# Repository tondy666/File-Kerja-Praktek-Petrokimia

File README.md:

File Laporan Kerja Praktek PT.PETROKIMIA GRESIK

© Copyright
Tondy_666

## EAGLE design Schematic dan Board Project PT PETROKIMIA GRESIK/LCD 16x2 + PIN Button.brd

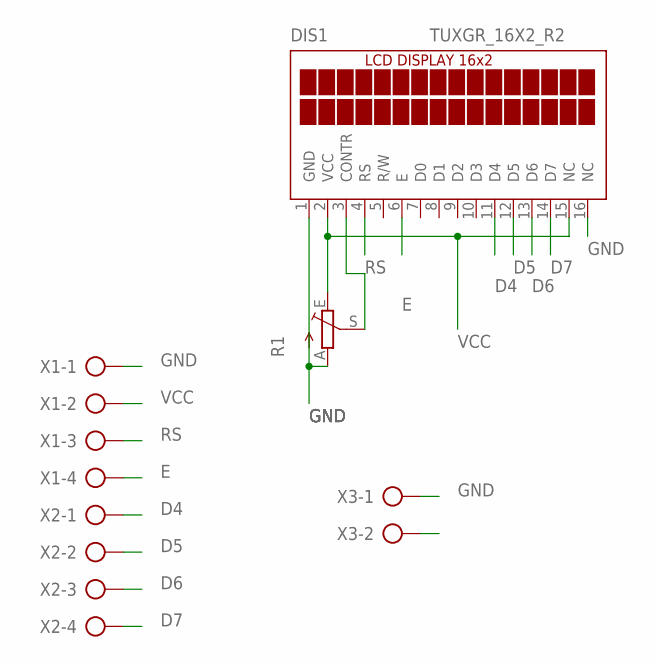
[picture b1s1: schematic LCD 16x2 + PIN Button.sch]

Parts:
DIS1: TUXGR_16X2_R2
R1: TRIM_EU-B25P; B25P
X1, X2: AK500/4-H
X3: AK500/2-H

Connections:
D4: DIS1.11 (D4), X2.1
D5: DIS1.12 (D5), X2.2
D6: DIS1.13 (D6), X2.3
D7: DIS1.14 (D7), X2.4
E: DIS1.6 (E), X1.4
GND: DIS1.1 (GND), DIS1.16 (NC), R1.A, X1.1, X3.1
unnamed: DIS1.3 (CONTR), R1.S
RS: DIS1.4 (RS), X1.3
VCC: DIS1.2 (VCC), DIS1.15 (NC), R1.E, X1.2

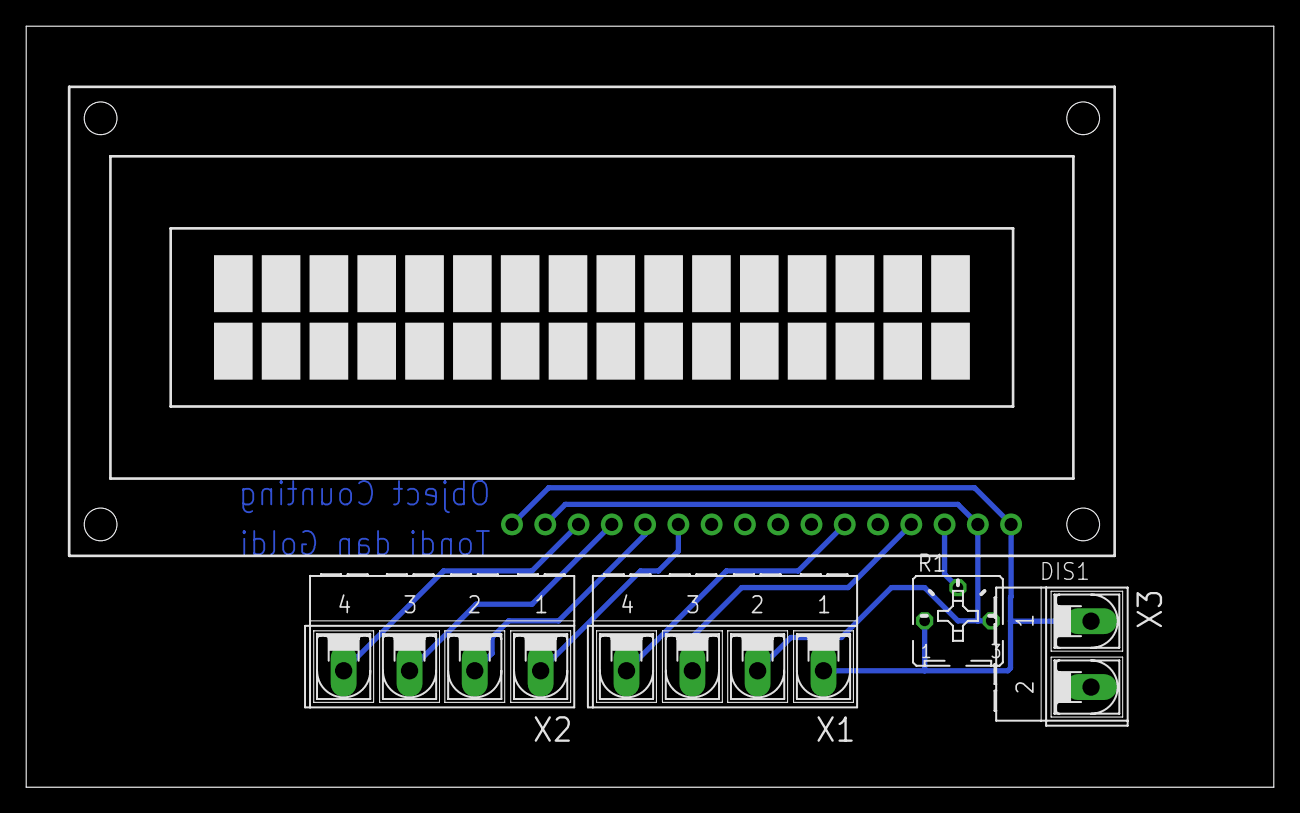
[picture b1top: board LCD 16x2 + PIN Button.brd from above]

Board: 2 copper layers, 95.2 x 58.1 mm, 5 parts (0 on the bottom side), 9 nets.

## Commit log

2020-02-10 Sudah Rev 1.1
2020-02-13 Revisi 1.3
2020-02-27 Revisi 1.5
2020-02-27 Menambahkan Seputar QnA Judul , Rumusan Masalah
2020-03-05 Menambahkan Revisi Latar Belakang
2020-03-10 Kata Pengantar belum fix v1.2
2020-03-10 Menambahkan Schematic dan Board LCD 16x2
2020-03-10 Menambahkan git ignore
2020-03-12 Menambahkan File Project dan PDF untuk di print
2020-03-23 Menambahkan Laporan Project OC Petrokimia Gresik
2020-03-23 Menambahkan Rekapan Kegiatanku cuy
2020-03-31 Revisi Fix v2.5
